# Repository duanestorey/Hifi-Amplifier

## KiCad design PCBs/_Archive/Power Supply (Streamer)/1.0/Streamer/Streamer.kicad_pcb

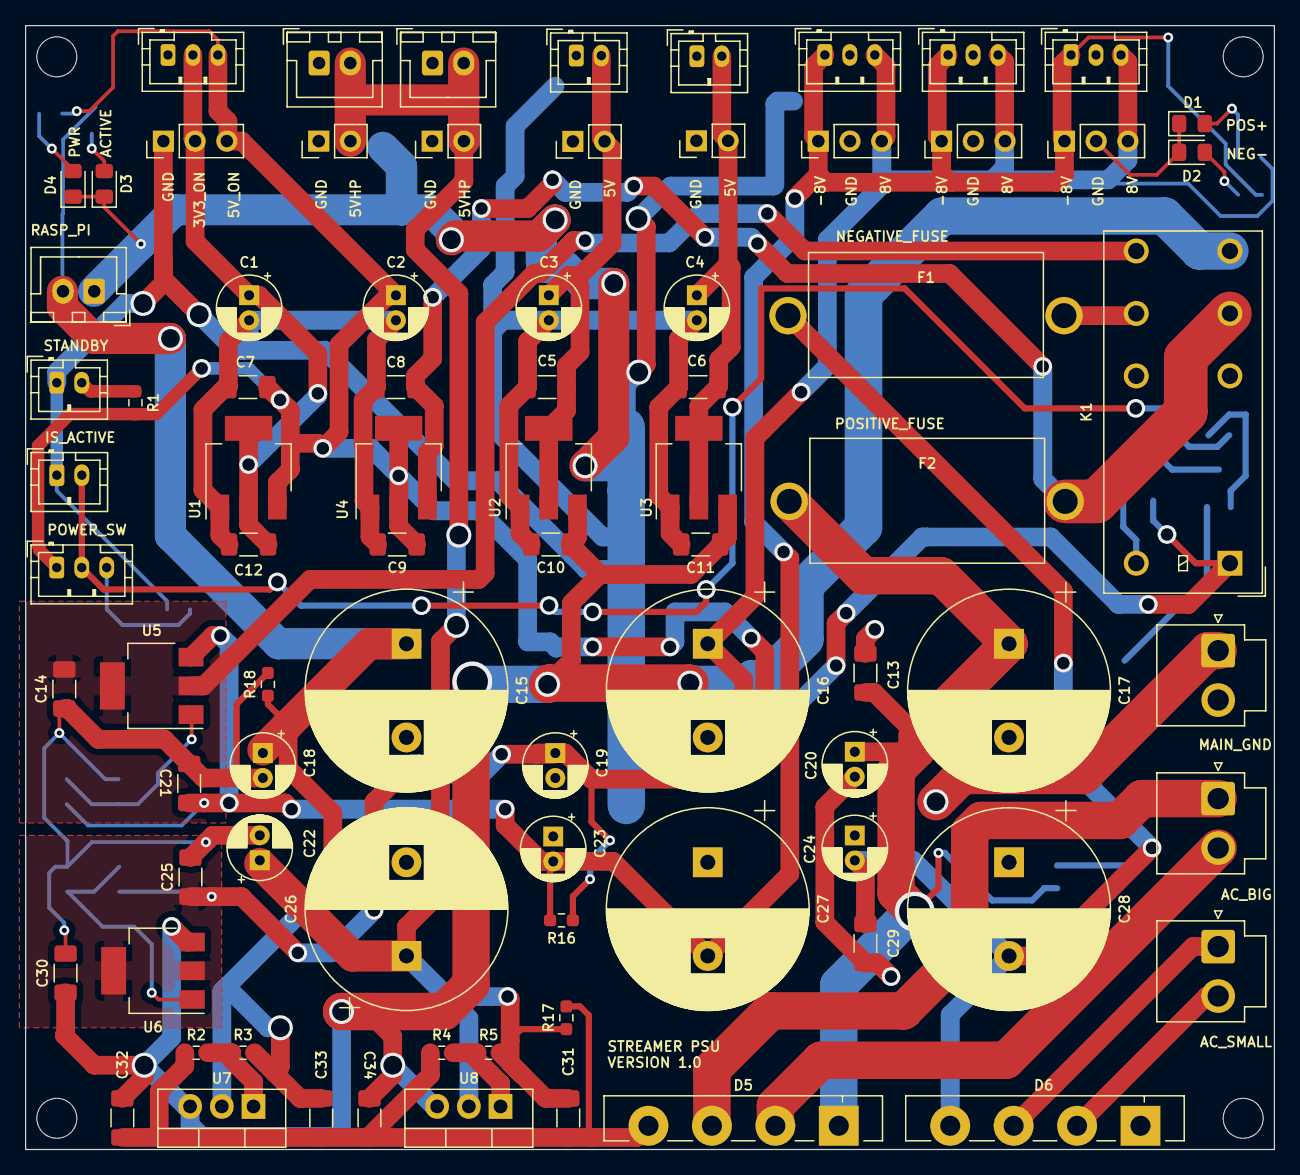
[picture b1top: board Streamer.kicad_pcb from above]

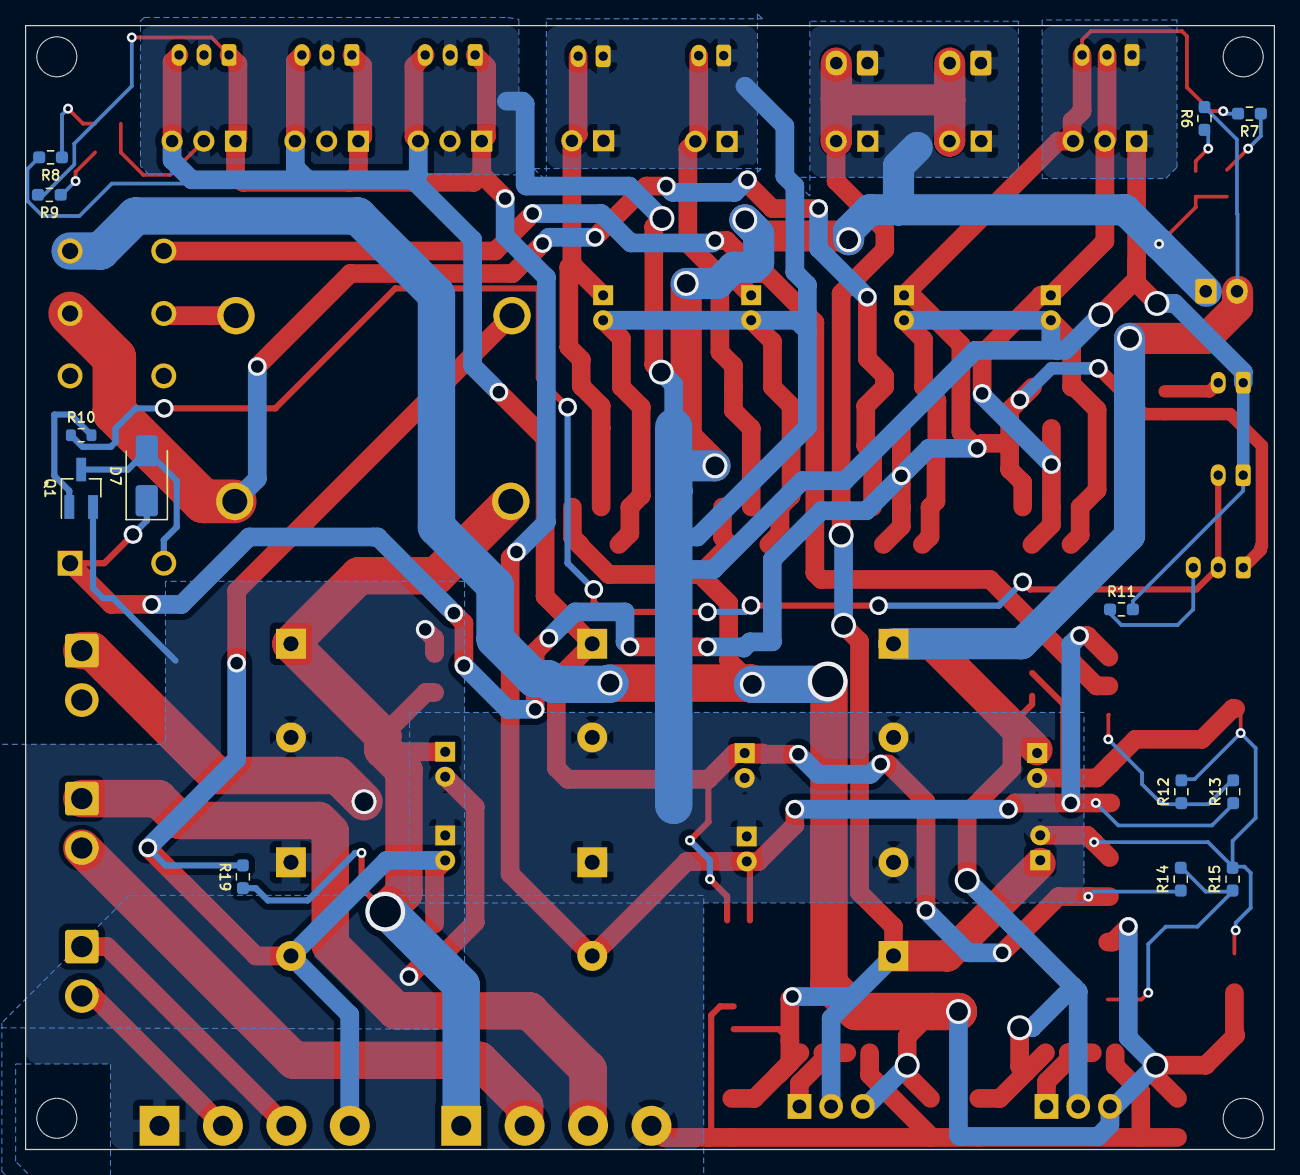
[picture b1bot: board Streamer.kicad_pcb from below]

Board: 2 copper layers, 100.0 x 90.0 mm, 99 parts (13 on the bottom side), 32 nets.

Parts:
C1, C2, C3, C4, C18, C19, C20, C22, C23, C24: 100uf; CP_Radial_D5.0mm_P2.00mm
C5, C6, C7, C8, C9, C10, C11, C12, C13, C14, C21, C25, C29, C30, C31, C32, C33, C34: 10u; C_1206_3216Metric_Pad1.33x1.80mm_HandSolder
C15, C16, C17, C26, C27, C28: 4700u; CP_Radial_D16.0mm_P7.50mm
D1: YELLOW; LED_0805_2012Metric_Pad1.15x1.40mm_HandSolder
D2, D3: BLUE; LED_0805_2012Metric_Pad1.15x1.40mm_HandSolder
D4: WHITE; LED_0805_2012Metric_Pad1.15x1.40mm_HandSolder
D5, D6: GBU4A; Diode_Bridge_Vishay_GBU
D7: 1N4001; D_SMA
F1, F2: Fuse; Aliexpress Fuse 5x20
H1, H2, H3, H4: MountingHole; MountingHole_3.2mm_M3
J1, J4, J5, J6, J20: Conn_01x03_Pin; JST_PH_B3B-PH-K_1x03_P2.00mm_Vertical
J2, J3, J17: Conn_01x02_Pin; JST_XH_B2B-XH-A_1x02_P2.50mm_Vertical
J7, J8, J18, J19: Conn_01x02_Pin; JST_PH_B2B-PH-K_1x02_P2.00mm_Vertical
J9, J13, J14, J15: Conn_01x03_Pin; PinHeader_1x03_P2.54mm_Vertical
J10, J11, J12, J16: Conn_01x02_Pin; PinHeader_1x02_P2.54mm_Vertical
J21, J22, J23: Conn_01x02_Pin; JST_VH_B2P-VH_1x02_P3.96mm_Vertical
K1: Relay_DPDT; Relay_DPDT_Omron_G2RL-2
Q1: 2SC1945; SOT-23_Handsoldering
R1, R7, R8, R11: 1K; R_0603_1608Metric_Pad0.98x0.95mm_HandSolder
R2, R4: 360R; R_0603_1608Metric_Pad0.98x0.95mm_HandSolder
R3, R5, R13, R14: 120R; R_0603_1608Metric_Pad0.98x0.95mm_HandSolder
R6, R9: 670R; R_0603_1608Metric_Pad0.98x0.95mm_HandSolder
R10: 1K; R_0603_1608Metric
R12, R15: 750R; R_0603_1608Metric_Pad0.98x0.95mm_HandSolder
R16: 3.5K; R_0603_1608Metric_Pad0.98x0.95mm_HandSolder
R17, R18: 6.7K; R_0603_1608Metric_Pad0.98x0.95mm_HandSolder
R19: 5.5K; R_0603_1608Metric_Pad0.98x0.95mm_HandSolder
U1: AMS1117-3.3; SOT-223-3_TabPin2
U2, U3: LDL1117; SOT-223-3_TabPin2
U4: AMS1117-5.0; SOT-223-3_TabPin2
U5: LM337_SOT223; SOT-223-3_TabPin2
U6: LM317_SOT-223; SOT-223-3_TabPin2
U7, U8: LM1084; TO-220-3_Vertical

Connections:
3V3_STATIC: C1.1, C12.1, J1.2, J9.2, U1.2 (VO)
5V_2: C3.1, C5.1, J7.2, J16.2, U2.2 (VO)
5V_3: C4.1, C6.1, J8.2, J12.2, U3.2 (VO)
5V_HP: C22.1, C26.1, C31.1, J2.2, J3.2, J10.2, J11.2, R5.2, R17.1, U8.2 (VO)
5V_PI: C15.1, C18.1, C33.1, J17.2, R3.2, R6.2, R18.1, U7.2 (VO)
5V_STATIC: C2.1, C7.1, C9.1, D7.1 (K), J1.3, J9.3, J20.1, K1.A1, R1.2, R7.2, U1.3 (VI), U4.2 (VO)
AC1_NEG: D5.2, J22.2
AC1_POS: D5.3, J22.1
AC2_NEG: D6.2, J23.2
AC2_POS: D6.3, J23.1
ACTIVATE: J19.2, J20.2, R10.1
AGND: C1.2, C2.2, C3.2, C4.2, C5.2, C6.2, C7.2, C8.2, C9.2, C10.2, C11.2, C12.2, C13.2, C14.1, C15.2, C16.2, C17.2, C18.2, C19.2, C20.2, C21.1, C22.2, C23.1, C24.1, C25.2, C26.2, C27.1, C28.1, C29.1, C30.2, C31.2, C32.2, C33.2, C34.2, D1.1 (K), D2.1 (K), D3.1 (K), D4.1 (K), D5.4 (-), D6.1 (+), J1.1, J2.1, J3.1, J4.2, J5.2, J6.2, J7.1, J8.1, J9.1, J10.1, J11.1, J12.1, J13.2, J14.2, J15.2, J16.1, J17.1, J18.1, J19.1, J21.1, Q1.2 (E), R2.1, R4.1, R11.2, R12.2, R15.2, R17.2, R18.2, U1.1 (GND), U2.1 (GND), U3.1 (GND), U4.1 (GND)
ANALOG_NEG: C21.2, C23.2, C27.2, J4.1, J5.1, J6.1, J13.1, J14.1, J15.1, R9.2, R13.1, R16.2, U5.3 (VO)
ANALOG_POS: C16.1, C19.1, C25.1, J4.3, J5.3, J6.3, J13.3, J14.3, J15.3, R8.2, R14.1, R16.1, U6.2 (VO)
DC_NEG: C14.2, K1.24, U5.2 (VI)
DC_NEG_PRE_RELAY: F1.2, K1.21
DC_POS: C10.1, C11.1, C30.1, C32.1, C34.1, K1.14, U2.3 (VI), U3.3 (VI), U6.3 (VI), U7.3 (VI), U8.3 (VI)
DC_POS_PRE_RELAY: C8.1, F2.2, K1.11, U4.3 (VI)
ENTRY_NEG: C24.2, C28.2, C29.2, D6.4 (-), F1.1, R19.2
ENTRY_POS: C13.1, C17.1, C20.1, D5.1 (+), F2.1, R19.1
unnamed: D1.2 (A), R8.1
unnamed: D2.2 (A), R9.1
unnamed: D3.2 (A), R6.1
unnamed: D4.2 (A), R7.1
unnamed: D7.2 (A), K1.A2, Q1.3 (C)
unnamed: J18.2, R1.1
unnamed: J20.3, R11.1
unnamed: Q1.1 (B), R10.2
unnamed: R12.1, R13.2, U5.1 (ADJ)
unnamed: R14.2, R15.1, U6.1 (ADJ)
unnamed: R2.2, R3.1, U7.1 (ADJ)
unnamed: R4.2, R5.1, U8.1 (ADJ)

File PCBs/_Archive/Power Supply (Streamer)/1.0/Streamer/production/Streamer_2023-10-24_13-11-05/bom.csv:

Designator,Footprint,Quantity,Value,LCSC Part #
"C1, C18, C19, C2, C20, C22, C23, C24, C3, C4",CP_Radial_D5.0mm_P2.00mm,10,100uf,
"C10, C11, C12, C13, C14, C21, C25, C29, C30, C31, C32, C33, C34, C5, C6, C7, C8, C9",1206,18,10u,
"C15, C16, C17, C26, C27, C28",CP_Radial_D16.0mm_P7.50mm,6,4700u,
D1,0805,1,YELLOW,
"D2, D3",0805,2,BLUE,
D4,0805,1,WHITE,
"D5, D6",Diode_Bridge_Vishay_GBU,2,GBU4A,
D7,D_SMA,1,1N4001,
"F1, F2",Aliexpress Fuse 5x20,2,Fuse,
"H1, H2, H3, H4",MountingHole_3.2mm_M3,4,MountingHole,
"J1, J20, J4, J5, J6",JST_PH_B3B-PH-K_1x03_P2.00mm_Vertical,5,Conn_01x03_Pin,
"J10, J11, J12, J16",PinHeader_1x02_P2.54mm_Vertical,4,Conn_01x02_Pin,
"J13, J14, J15, J9",PinHeader_1x03_P2.54mm_Vertical,4,Conn_01x03_Pin,
"J17, J2, J3",JST_XH_B2B-XH-A_1x02_P2.50mm_Vertical,3,Conn_01x02_Pin,
"J18, J19, J7, J8",JST_PH_B2B-PH-K_1x02_P2.00mm_Vertical,4,Conn_01x02_Pin,
"J21, J22, J23",JST_VH_B2P-VH_1x02_P3.96mm_Vertical,3,Conn_01x02_Pin,
K1,Relay_DPDT_Omron_G2RL-2,1,Relay_DPDT,
Q1,SOT-23_Handsoldering,1,2SC1945,
"R1, R10, R11, R7, R8",0603,5,1K,
"R12, R15",0603,2,750R,
"R13, R14, R3, R5",0603,4,120R,
R16,0603,1,3.5K,
"R17, R18",0603,2,6.7K,
R19,0603,1,5.5K,
"R2, R4",0603,2,360R,
"R6, R9",0603,2,670R,
U1,SOT-223-3_TabPin2,1,AMS1117-3.3,
"U2, U3",SOT-223-3_TabPin2,2,LDL1117,
U4,SOT-223-3_TabPin2,1,AMS1117-5.0,
U5,SOT-223-3_TabPin2,1,LM337_SOT223,
U6,SOT-223-3_TabPin2,1,LM317_SOT-223,
"U7, U8",TO-220-3_Vertical,2,LM1084,

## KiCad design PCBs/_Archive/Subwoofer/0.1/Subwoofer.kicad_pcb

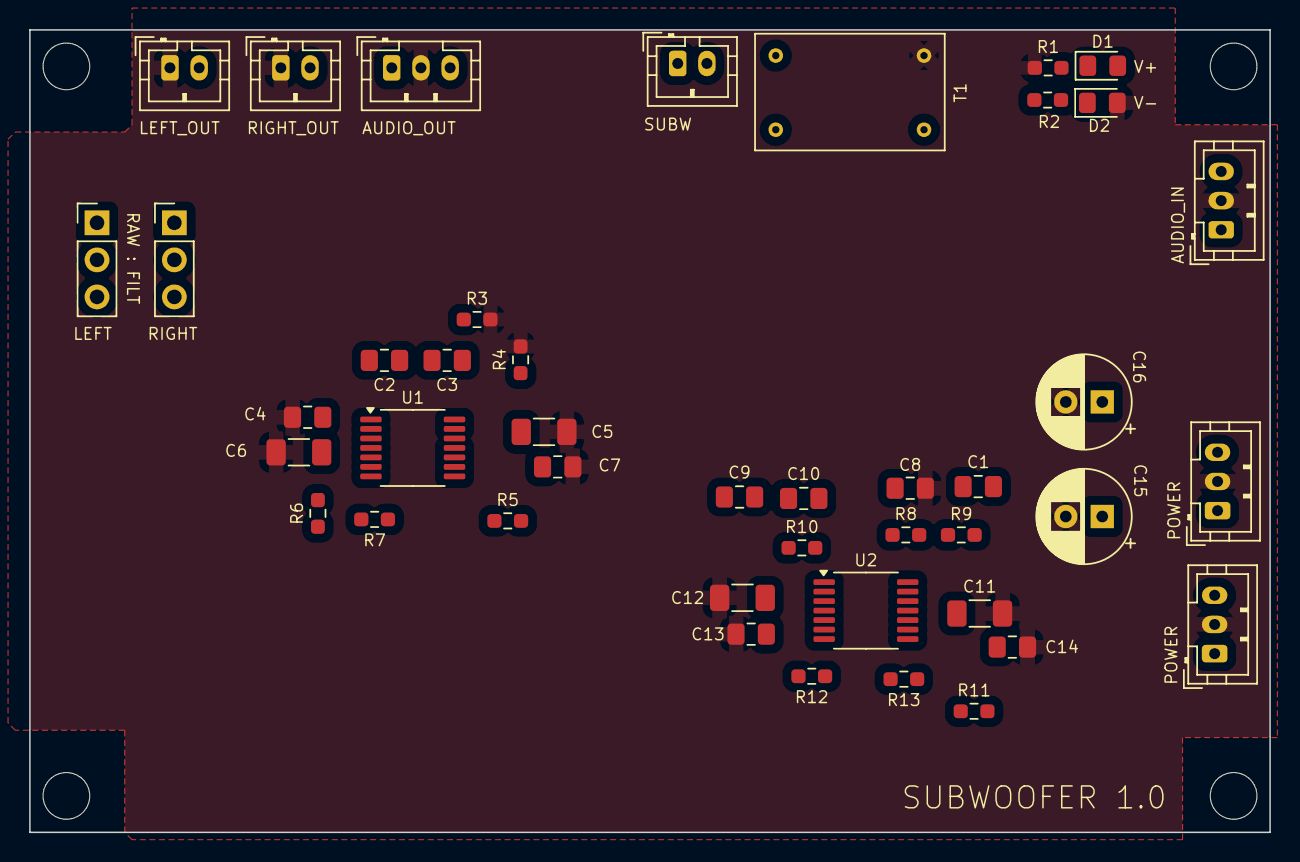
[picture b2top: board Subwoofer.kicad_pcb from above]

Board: 2 copper layers, 85.0 x 55.0 mm, 47 parts (0 on the bottom side), 29 nets, no tracks yet.

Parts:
C1, C2, C3, C9, C10: 200N C0G; C_0805_2012Metric_Pad1.18x1.45mm_HandSolder
C4, C7, C13, C14: 0.1U; C_0805_2012Metric_Pad1.18x1.45mm_HandSolder
C5, C6, C11, C12: 10U; C_1206_3216Metric_Pad1.33x1.80mm_HandSolder
C8: 91N C0G; C_0805_2012Metric_Pad1.18x1.45mm_HandSolder
C15, C16: 470u; CP_Radial_D6.3mm_P2.50mm
D1: YELLOW; LED_0805_2012Metric_Pad1.15x1.40mm_HandSolder
D2: BLUE; LED_0805_2012Metric_Pad1.15x1.40mm_HandSolder
H1, H2, H3, H4: MountingHole; MountingHole_3.2mm_M3
J1, J2, J3: Conn_01x02_Pin; JST_PH_B2B-PH-K_1x02_P2.00mm_Vertical
J4, J5: Conn_01x03_Pin; PinHeader_1x03_P2.54mm_Vertical
J6, J8: Conn_01x03_Male; JST_PH_B3B-PH-K_1x03_P2.00mm_Vertical
J7, J10: Conn_01x03_Pin; JST_PH_B3B-PH-K_1x03_P2.00mm_Vertical
R1: 1.25K; R_0603_1608Metric_Pad0.98x0.95mm_HandSolder
R2: 1K; R_0603_1608Metric_Pad0.98x0.95mm_HandSolder
R3, R4, R5, R6: 6.8K; R_0603_1608Metric_Pad0.98x0.95mm_HandSolder
R7: 25k; R_0603_1608Metric_Pad0.98x0.95mm_HandSolder
R8: 20K; R_0603_1608Metric_Pad0.98x0.95mm_HandSolder
R9: 11K; R_0603_1608Metric_Pad0.98x0.95mm_HandSolder
R10, R11, R12, R13: 25K; R_0603_1608Metric_Pad0.98x0.95mm_HandSolder
T1: Transformer_Audio; DA101C
U1, U2: Opamp_Quad; TSSOP-14_4.4x5mm_P0.65mm

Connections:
AGND: C4.2, C5.2, C6.2, C7.2, C8.1, C11.2, C12.2, C13.2, C14.2, C15.2, C16.2, D2.2 (A), J2.1, J3.1, J6.2, J7.2, J8.2, J10.2, R1.1, R3.2, R4.2, T1.2 (AB), U1.12 (+)
LEFT_FILT: J5.3, R5.1, U1.8, U1.9 (-)
LEFT_IN: J5.1, J10.1, U2.3 (+)
LEFT_OUT: J3.2, J5.2, J7.1
unnamed: C1.2, R8.2, R9.1
unnamed: C2.1, C3.2, R6.2
unnamed: C9.2, C10.1, R5.2
unnamed: D1.1 (K), R1.2
unnamed: D2.1 (K), R2.2
unnamed: R10.1, R13.2, U2.7
unnamed: R9.2, R11.1, U2.8
unnamed: C2.2, R7.2, U1.1, U1.2 (-)
unnamed: C3.1, R3.1, U1.5 (+)
unnamed: C9.1, R4.1, U1.10 (+)
unnamed: U1.13 (-), U1.14
unnamed: C10.2, R12.2, U2.1, U2.2 (-)
unnamed: R10.2, U2.5 (+)
unnamed: R7.1, R12.1, U2.6 (-)
unnamed: R11.2, U2.10 (+)
unnamed: R13.1, U2.9 (-)
unnamed: C8.2, R8.1, U2.12 (+)
RIGHT_FILT: J4.3, R6.1, U1.6 (-), U1.7
RIGHT_IN: J4.1, J10.3, U1.3 (+)
RIGHT_OUT: J2.2, J4.2, J7.3
SUBW: C1.1, T1.1 (AA), U2.13 (-), U2.14
SUBWN: J1.1, T1.3 (SA)
SUBWP: J1.2, T1.4 (SB)
V+: C4.1, C6.1, C12.1, C13.1, C15.1, D1.2 (A), J6.3, J8.3, U1.4 (V+), U2.4 (V+)
V-: C5.1, C7.1, C11.1, C14.1, C16.1, J6.1, J8.1, R2.1, U1.11 (V-), U2.11 (V-)
